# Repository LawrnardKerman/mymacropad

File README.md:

# my silly macropad
silly macropad :3

onshape link: https://cad.onshape.com/documents/43d22975be5866152dda32ee/w/25548284fc252923895191e8/e/8e7716d520c439ebb7f659c6?renderMode=0&uiState=6a9d54876a2ca21d8aef6d35

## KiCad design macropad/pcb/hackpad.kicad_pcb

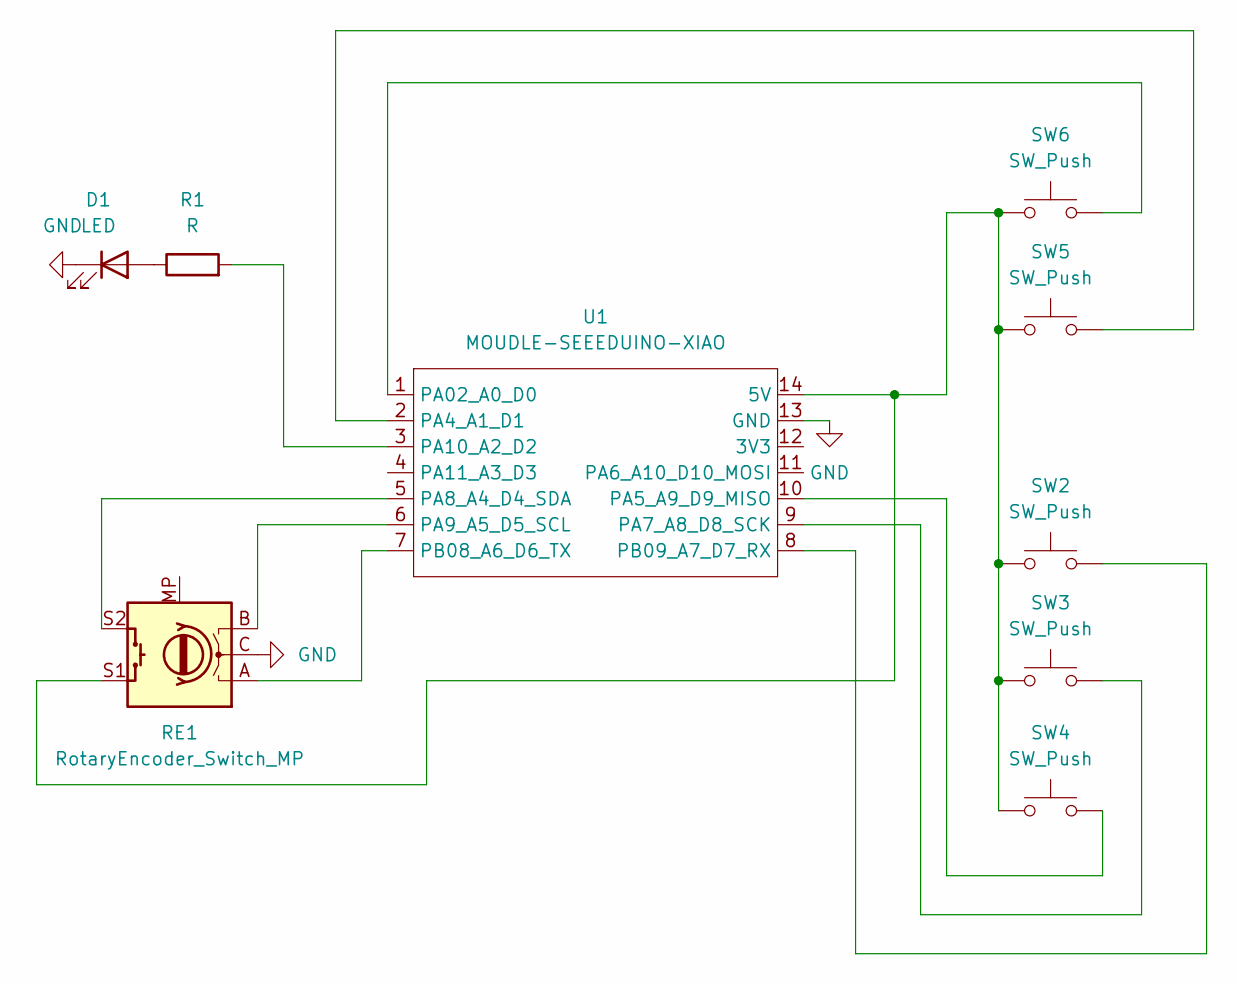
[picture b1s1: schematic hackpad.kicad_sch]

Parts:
D1: LED; LED_Yuji_5730
R1: R; R_0201_0603Metric_Pad0.64x0.40mm_HandSolder
RE1: RotaryEncoder_Switch_MP; RotaryEncoder_Alps_EC11E-Switch_Vertical_H20mm
SW2, SW3, SW4, SW5, SW6: SW_Push; SW_Cherry_MX_1.00u_PCB
U1: MOUDLE-SEEEDUINO-XIAO; XIAO-Generic-Hybrid-14P-2.54-21X17.8MM

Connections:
GND: D1.1 (K), RE1.C, U1.13 (GND)
unnamed: D1.2 (A), R1.1
unnamed: RE1.S1, SW2.1, SW3.1, SW4.1, SW5.1, SW6.1, U1.14 (5V)
unnamed: SW6.2, U1.1 (PA02_A0_D0)
unnamed: SW5.2, U1.2 (PA4_A1_D1)
unnamed: SW4.2, U1.10 (PA5_A9_D9_MISO)
unnamed: SW3.2, U1.9 (PA7_A8_D8_SCK)
unnamed: RE1.S2, U1.5 (PA8_A4_D4_SDA)
unnamed: RE1.B, U1.6 (PA9_A5_D5_SCL)
unnamed: R1.2, U1.3 (PA10_A2_D2)
unnamed: RE1.A, U1.7 (PB08_A6_D6_TX)
unnamed: SW2.2, U1.8 (PB09_A7_D7_RX)

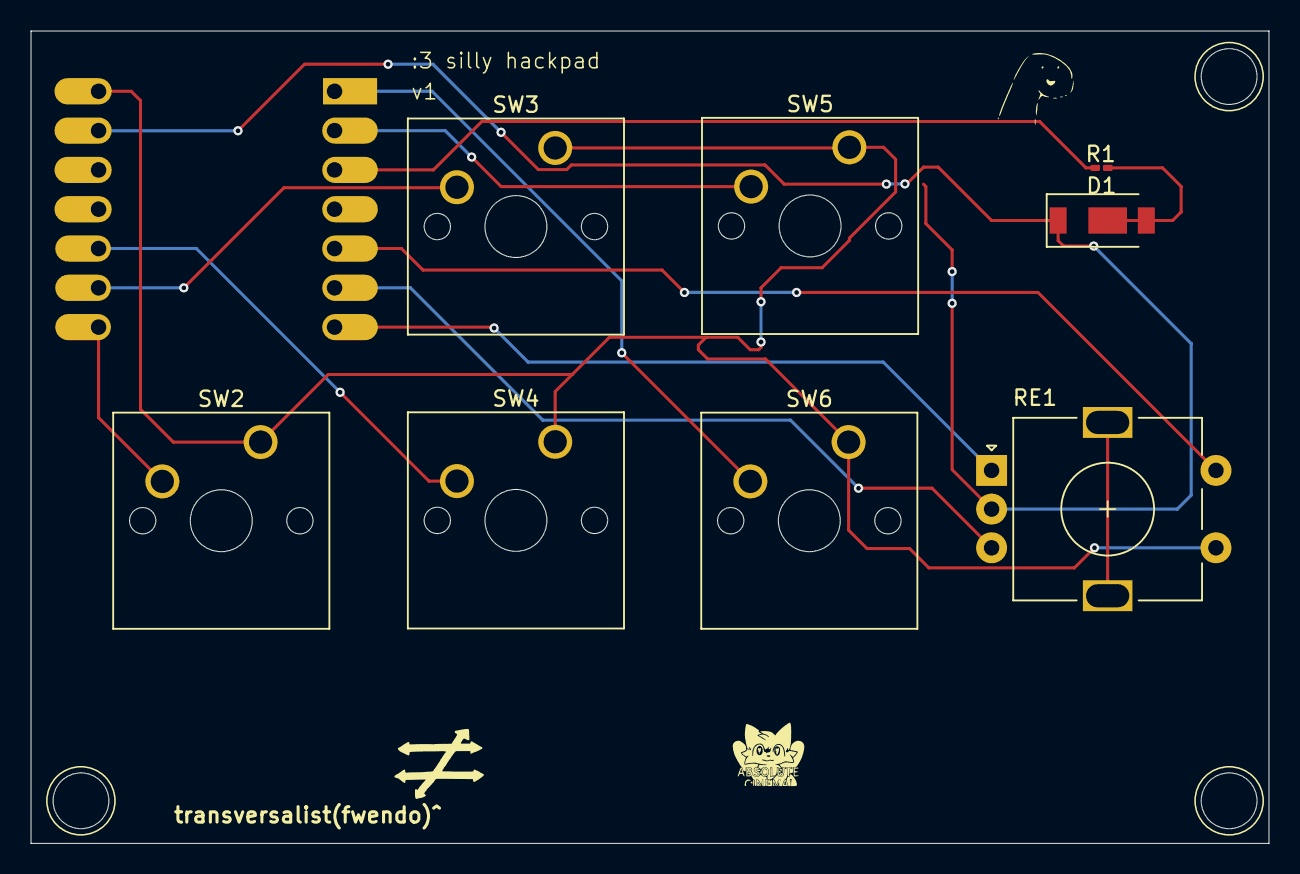
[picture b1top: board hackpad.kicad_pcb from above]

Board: 2 copper layers, 80.0 x 52.5 mm, 9 parts (1 on the bottom side), 12 nets.

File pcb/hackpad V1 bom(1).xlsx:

part # | Qty | Ref Des | Manf Part Num | desc, | manf name | Do not install | type
1.0 | 5.0 | SW1, SW2, SW3, SW4, SW5 | MX2A-11DN | mx mechanical switch | mx cherry | DNI | tht
2.0 | 1.0 | R1 | C2075596 | 0201 smd 470 ohm resistor | TE Connectivity |  | smd
3.0 | 1.0 | D1 | C210346 | 5730 smd led | HONGLITRONIC(Hongli Zhihui (HONGLITRONIC)) |  | smd
4.0 | 1.0 | RE1 | EC11E18244AU | ec11 rotary encoder | alps alpine | DNI | tht
5.0 | 1.0 | U1 | 1.02010428E8 | seeed sudio xiao rp 2040 | seeed studio | DNI | smd
